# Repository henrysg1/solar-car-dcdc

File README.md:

# DC-DC Converter for Solar Car

## Overview

This repository contains the design files for a DC-DC converter used in the University of Nottingham's solar race car. The converter steps down the battery voltage from 135V to 12V, which is essential for powering various low-voltage components in the vehicle.

## Features

- **Input Voltage:** 135V
- **Output Voltage:** 12V
- **Output Current:** Up to 50A
- **Efficiency:** > 90%
- **Protection:** Overvoltage, Overcurrent, Thermal Shutdown
- **Compact PCB Design**

## Status

The PCB revision in this repository has been manufactured and succesfully tested and implemented in the solar car, verifying that the system works as intended.

## Getting Started

### Prerequisites

To work with the design files, you will need:

- [KiCad](https://kicad.org/) for schematic and PCB design. **Important Note: For this project, a Nightly Development Build of KiCAD has been used (6.99). The project will not work on a Stable Version release (6.00)**

### Usage

1. Clone the repository:
   ```bash
   git clone https://github.com/yourusername/dcdc-converter-solar-car.git
   cd dcdc-converter-solar-car
   ```
2. Include the component files in the KiCAD project (in the 'Component Files' folder)
3. Open the schematic file (dcdc_converter.sch) in KiCad.
4. Open the PCB layout file (dcdc_converter.kicad_pcb) in KiCad.

## Schematic

The schematic for the DC-DC converter is designed to step down the voltage from 135V to 12V. Here are the key sections and components:

### Input Section
- **J2, J3 (Connectors):** These connectors receive the high voltage (135V) input.
- **F1, F2 (5A Fuses):** Provide overcurrent protection for the high voltage input.

### Relay Control
- **K1 (Relay):** This relay enables or disables the DC-DC converter based on an external switch connected through IPL1.
- **D1 (Diode):** Acts as a flyback diode for the relay coil, protecting against voltage spikes.

### Primary Conversion Stage
- **L1, L2 (1µH Inductors):** Form LC filters along with C1 and C2 to smooth the input voltage.
- **R1, R2 (1Ω Resistors):** Used for current sensing in the primary stage.

### DC-DC Converter Modules
- **PS1, PS2 (DCM3623T5N13B4T00):** These modules handle the main conversion from high to low voltage. They include control and feedback components:
  - **R5, R6 (510Ω, 50kΩ Resistors)**
  - **RV1, RV2 (250kΩ Potentiometers)**
  - **D3, D4 (LTST-C193KRKT-5A Diodes)**

### Output Section
- **L3, L4 (0.15µH Inductors):** Further filter the output voltage.
- **C3, C4 (1000µF Capacitors):** Stabilize the output voltage.
- **F4, F5 (25A Fuses):** Provide overcurrent protection for the output.
- **J4 (Output Connector):** The connector for accessing the stepped-down 12V output.

This design ensures efficient voltage conversion with necessary protections for both input and output stages.

## PCB Layout

The PCB layout is designed to maximise efficiency and handle high current traces. Key considerations include:

- Trace Widths: Sized appropriately for current handling.
- Component Placement: Optimised for thermal management and isolating voltages.
- Ground Plane: Ensures low impedance return paths.

## License
This project is licensed under the MIT License. See the LICENSE file for details.

## Acknowledgments
University of Nottingham Solar Race Team \
KiCad Community

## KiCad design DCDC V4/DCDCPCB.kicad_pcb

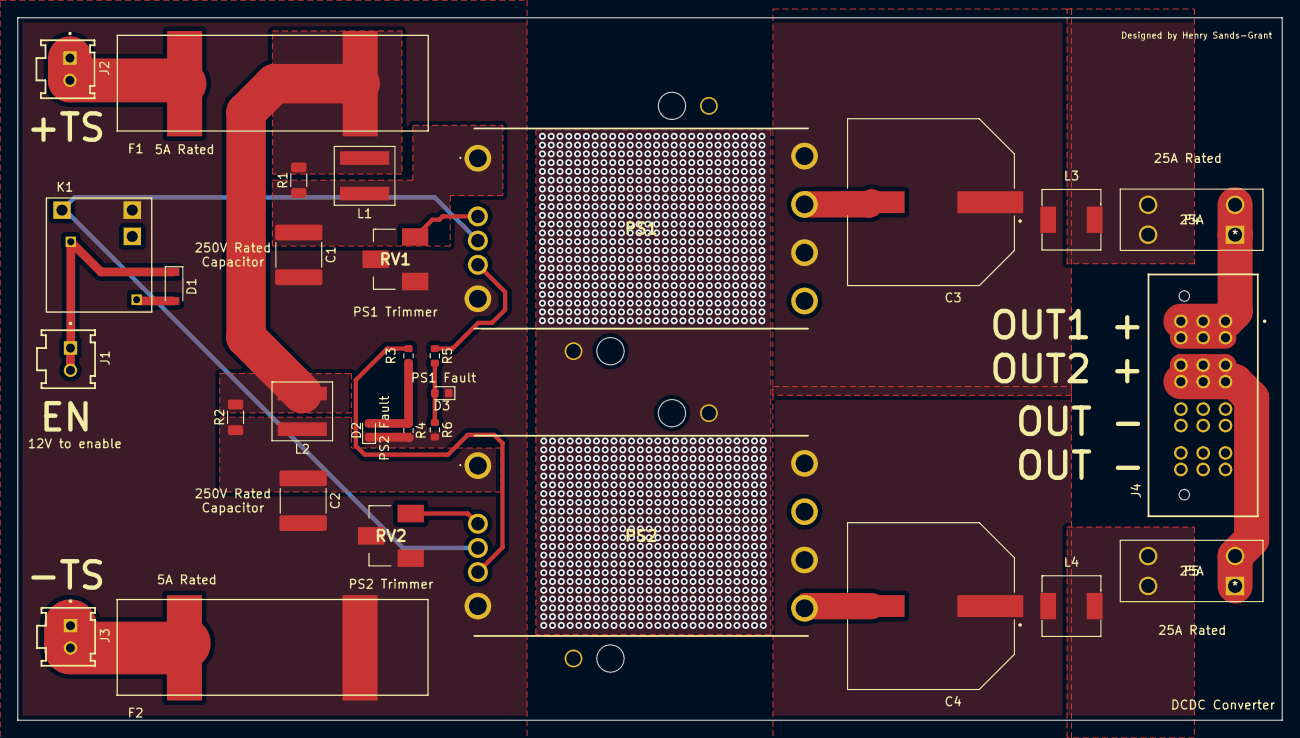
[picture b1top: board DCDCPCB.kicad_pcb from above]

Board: 2 copper layers, 144.0 x 80.0 mm, 31 parts (1 on the bottom side), 22 nets.

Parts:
C1, C2: 2uF; C_2220_5650Metric
C3, C4: 1000uF; CAP_EEVTG1E102M
D1: D_SOD-123
D2, D3: LTST-C193KRKT-5A; LED_0603_1608Metric
F1, F2: 5A; PCB_Fuse_Holder_MC_69_0013
F3: 1A; D_1206_3216Metric
F4, F5: 25A; 3568
J1, J2, J3: IPL1; SAMTEC_IPL1-102-01-L-S-K
J4: MPT-04; SAMTEC_MPT-04-6.30-XX-X-V
K1: RELAY_SPDT; Micro_Relay_V23086C1001A403
L1, L2: 1uH; 1uHInductor
L3, L4: 0.15uH; 0.15UInductor
PS1, PS2: DCM3623TA5N13B4T00; DCM3623TA5N13B4T00Heatsink
R1, R2: 1; R_1206_3216Metric
R3, R5: 510; R_0603_1608Metric
R4, R6: 50k; R_0603_1608Metric
RV1, RV2: 250k; TS63Y254KT20

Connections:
/Earth(chassis): D1.2 (A), K1.2
/Out1+: F4.1, J4.P01_1 (P01), J4.P01_2 (P01), J4.P01_3 (P01), J4.P01_4 (P01), J4.P01_5 (P01), J4.P01_6 (P01)
/Out2+: F5.1, J4.P02_1 (P02), J4.P02_2 (P02), J4.P02_3 (P02), J4.P02_4 (P02), J4.P02_5 (P02), J4.P02_6 (P02)
/Out-: C3.2, C4.2, F3.2, J4.P03_1 (P03), J4.P03_2 (P03), J4.P03_3 (P03), J4.P03_4 (P03), J4.P03_5 (P03), J4.P03_6 (P03), J4.P04_1 (P04), J4.P04_2 (P04), J4.P04_3 (P04), J4.P04_4 (P04), J4.P04_5 (P04), J4.P04_6 (P04), PS1.B2 (-OUT_1), PS1.D2 (-OUT_2), PS2.B2 (-OUT_1), PS2.D2 (-OUT_2)
/~Disable: K1.4 (C1), PS1.C1 (EN), PS2.C1 (EN)
GND: C1.2, C2.2, D2.1 (K), D3.1 (K), F2.1, F3.1, K1.3 (R1), PS1.E1 (-IN), PS2.E1 (-IN), R4.2, R6.2, RV1.2, RV1.3, RV2.2, RV2.3
unnamed: D1.1 (K), J1.1, J1.2, K1.1
unnamed: D2.2 (A), R3.2, R4.1
unnamed: D3.2 (A), R5.2, R6.1
unnamed: F1.1, L1.1, L2.1, R1.2, R2.2
unnamed: F1.2, J2.1, J2.2
unnamed: F2.2, J3.1, J3.2
unnamed: F4.2, L3.2
unnamed: F5.2, L4.2
unnamed: C1.1, L1.2, PS1.A1 (+IN), R1.1
unnamed: C3.1, L3.1, PS1.A2 (+OUT_1), PS1.C2 (+OUT_2)
unnamed: PS1.D1 (FT), R5.1
unnamed: PS1.B1 (TR), RV1.1
unnamed: C2.1, L2.2, PS2.A1 (+IN), R2.1
unnamed: C4.1, L4.1, PS2.A2 (+OUT_1), PS2.C2 (+OUT_2)
unnamed: PS2.D1 (FT), R3.1
unnamed: PS2.B1 (TR), RV2.1

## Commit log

2024-05-28 Updating file directories
2024-05-28 Create LICENSE
2025-01-01 Updating schematic for voltage

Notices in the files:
parts and their libraries:
Copyright 2021 Accelerated Designs. All rights reserved.
